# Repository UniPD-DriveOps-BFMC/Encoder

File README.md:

<h2>
⚠️ Manufacturer recommends no more than three cycles of mounting and removal of the AMT top cover base. Multiple cycles can cause base fatigue over time and make the base break, affecting encoder performance. It is advised to remove the encoder together with the mounting bracket as a whole from the car.
</h2>
<h3>
ALGORITHM
</h3>
  
1. Read encoder count difference from timer
2. Add this difference to total encoder count
3. Apply drift correction using Z index: **Z CORRECTION**
   - Compute position error relative to one full revolution
   - Apply a small correction to the encoder offset
   - Update corrected encoder counts
4. Convert corrected counts to distance
5. Calculate speed using change in distance over time
6. If speed is very small, set it to zero
7. Apply low-pass filter to smooth the speed: **VELOCITY_LPF**
8. If filtered speed is very small, set it to zero
9. Integrate filtered speed over time to get filtered distance
10. Differentiate filtered speed over time to get acceleration
11. Store current values to use in the next iteration

Change **Z_CORRECTION_GAIN** and **VELOCITY_LPF_ALPHA** as needed!

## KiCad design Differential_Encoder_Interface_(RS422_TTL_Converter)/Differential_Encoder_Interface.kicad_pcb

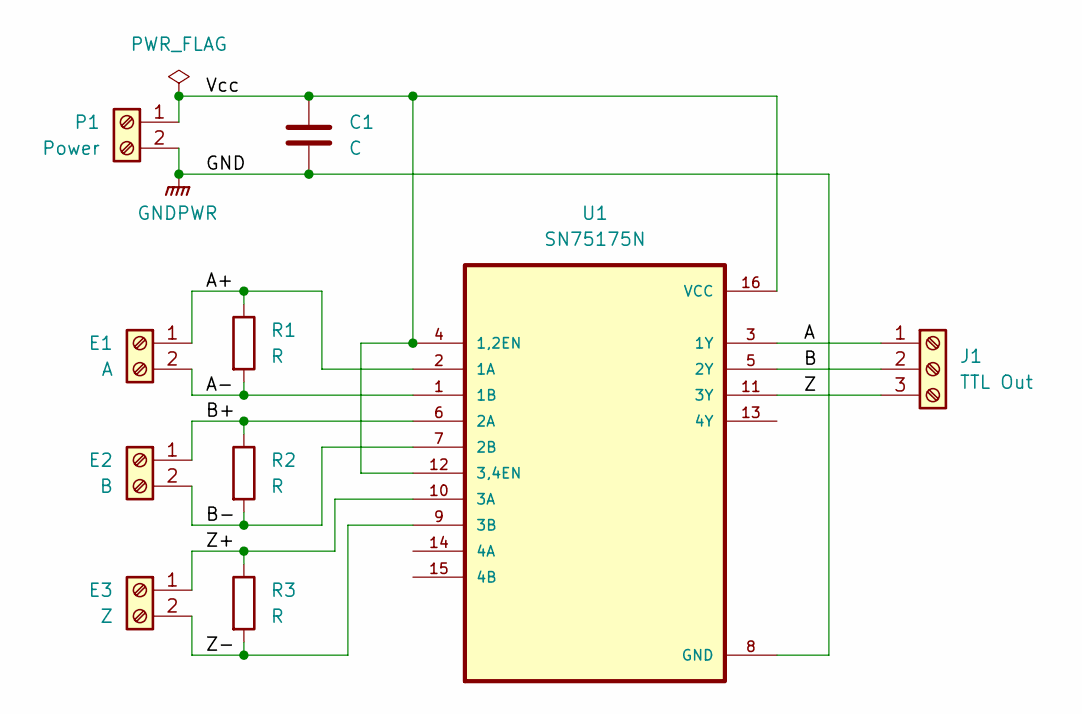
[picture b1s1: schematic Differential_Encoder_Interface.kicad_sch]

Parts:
C1: C; CP_Axial_L11.0mm_D5.0mm_P18.00mm_Horizontal
E1: A; TerminalBlock_MaiXu_MX126-5.0-02P_1x02_P5.00mm
E2: B; TerminalBlock_MaiXu_MX126-5.0-02P_1x02_P5.00mm
E3: Z; TerminalBlock_MaiXu_MX126-5.0-02P_1x02_P5.00mm
J1: TTL Out; TerminalBlock_MaiXu_MX126-5.0-03P_1x03_P5.00mm
P1: Power; TerminalBlock_MaiXu_MX126-5.0-02P_1x02_P5.00mm
R1, R2, R3: R; R_Axial_DIN0207_L6.3mm_D2.5mm_P7.62mm_Horizontal
U1: SN75175N; DIP-16_W7.62mm

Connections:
/A_N: E1.2, R1.2, U1.1 (1B)
/A_P: E1.1, R1.1, U1.2 (1A)
/B_N: E2.2, R2.2, U1.7 (2B)
/B_P: E2.1, R2.1, U1.6 (2A)
/C_N: E3.2, R3.2, U1.9 (3B)
/C_P: E3.1, R3.1, U1.10 (3A)
GNDPWR: C1.2, P1.2, U1.8 (GND)
unnamed: J1.1, U1.3 (1Y)
unnamed: J1.2, U1.5 (2Y)
unnamed: J1.3, U1.11 (3Y)
unnamed: C1.1, P1.1, U1.4 (1,2EN), U1.12 (3,4EN), U1.16 (VCC)

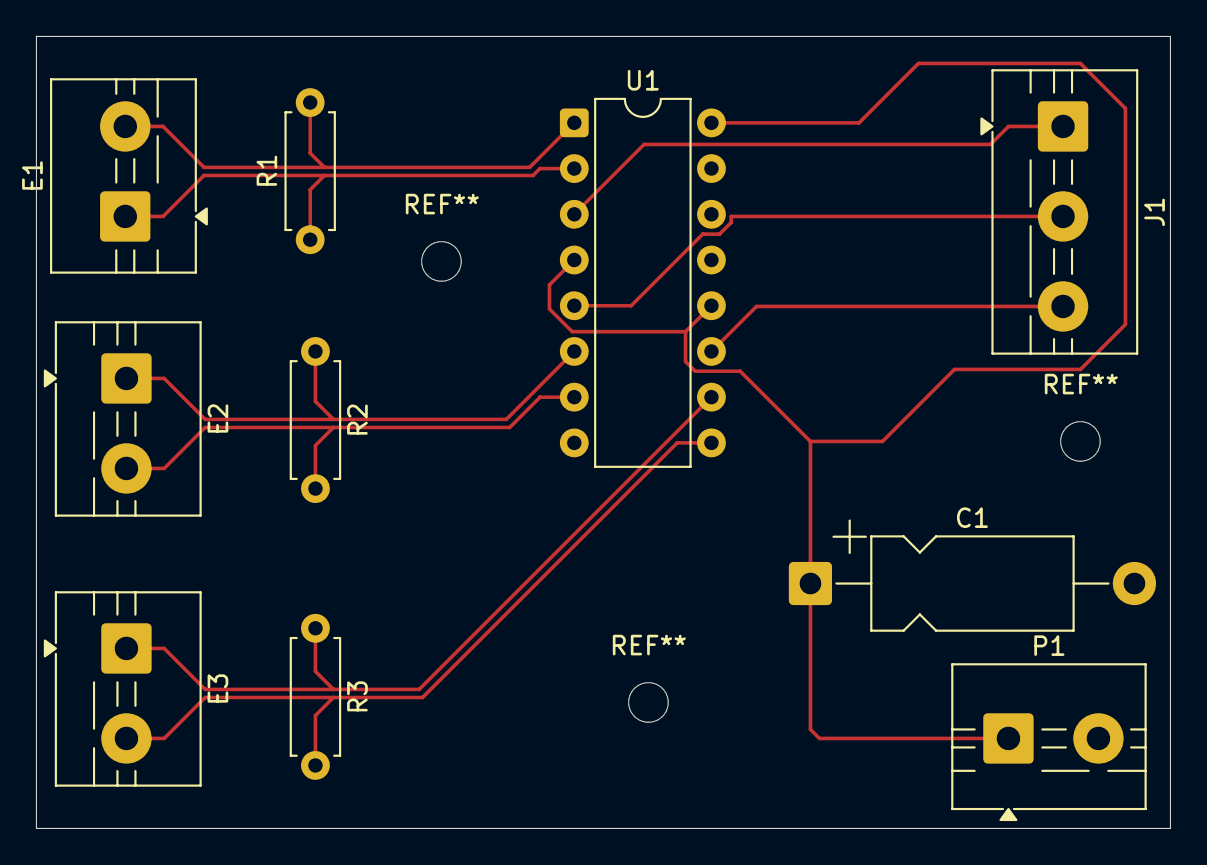
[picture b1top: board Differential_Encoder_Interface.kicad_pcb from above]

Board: 2 copper layers, 63.0 x 44.0 mm, 10 parts (0 on the bottom side), 11 nets.

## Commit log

2026-04-30 warning to README
    Add warning about mounting and removal cycles for AMT top cover base.
2026-04-30 README update
    Added folder description and usage notes for encoder.
2026-04-30 Fix formatting of bullet points in README.md
2026-05-04 Encoder Updated Final
2026-05-04 Document encoder algorithm and correction steps
    Added algorithm steps for encoder processing and corrections.
